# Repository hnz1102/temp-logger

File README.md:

<div align="center">
  <h1><code>Temperature Logger for K-Type Thermocouple</code></h1>
  
</div>

# TempLogger - Temperature Logger for K-Type Thermocouple

This board provides a logging function that gets data on temperature from a K-type thermocouple.

# Feature

**Microcontroller on board** - No need for a PC when you are measuring a temperature.

**Transfer Temperature data via WiFi** - This Logger can transfer temperature data to Linux PC via WiFi network and you can see the dashboard graph in influxDB.

**Battery Powered** - Using LiPo battery. It can run for 48 hours.

# How to use the TempLogger
Put on the thermocouple where you want to measure the temperature.  

Push the START/STOP button, then TempLogger starts to log the temperature. And if you want to send data on temperature, push the SEND button. During the measurement, TempLogger can send the data to a PC. 

A display can show you the current temperature, battery voltage, and WiFi connection status.

If WiFi could not connect to WiFi Access Point, the WiFi mark won't be shown on the display.

You can see the realtime data using Dashboard by [InfluxDB](https://www.influxdata.com/influxdb/).

After the measure, to stop logging, push the START/STOP button again.

To charge a battery, just connect to a USB mini-B port from the bus-powered USB port. During the charge, the CHG LED is RED ON. After the charging is full, the FUL LED is GREEN ON. And the charging will be stopped automatically. But, 

DO NOT CONTINUE THE CHARGE IF THE BATTERY IS FULL FOR A LONG TIME. 

# Case

There are data for 3D printer in `hardware/*.stl`.

# How to build code

Using Ubuntu 22.04.02 LTS

1. Install Rust Compiler
```bash
$ sudo apt -y install git python3 python3-pip gcc build-essential curl pkg-config libudev-dev libtinfo5 clang libclang-dev llvm-dev udev
$ curl --proto '=https' --tlsv1.2 -sSf https://sh.rustup.rs | sh
select No.1
$ source "$HOME/.cargo/env"
```

2. Install toolchain for ESP32-C3
```bash
$ cargo install ldproxy
$ cargo install espup
$ rustup toolchain install nightly --component rust-src
$ rustup target add riscv32imc-unknown-none-elf
$ cargo install cargo-espflash
```

3. Add UDEV rules
```bash
$ sudo sh -c 'echo "SUBSYSTEMS==\"usb\", ATTRS{idVendor}==\"303a\", ATTRS{idProduct}==\"1001\", MODE=\"0666\"" > /etc/udev/rules.d/99-esp32.rules'
$ sudo udevadm control --reload-rules
$ sudo udevadm trigger
```

4. Download Temp-Logger code
```bash
$ git clone https://github.com/hnz1102/temp-logger.git
$ cd temp-logger/src/temp-logger
``` 
5. Setting WiFi SSID, Password, and InfluxDB server IP address.
```bash
src\temp-logger\cfg.toml

[templogger]
wifi_ssid = "<your-AP-ssid>"     # Set your AP ssid.
wifi_psk = "<your-AP-Password>"  # Set password for ssid
http_server = "<PC address>:3000" # Set IP address and port. port should be 3000.
```

6. Connecting the board and Set device and set toolchain.
```bash
Connecting the Temp-Logger by USB to this build code PC. Then, 
$ cargo espflash board-info
select /dev/ttyACM0
Chip type:         esp32c3 (revision v0.4)
Crystal frequency: 40MHz
Flash size:        4MB
Features:          WiFi, BLE
MAC address:       xx:xx:xx:xx:xx:xx

$ rustup component add rust-src --toolchain nightly-2023-06-10-x86_64-unknown-linux-gnu
```

7. Build code and writing flash
```bash
$ cargo espflash flash --release --monitor
App/part. size:    950,864/3,145,728 bytes, 30.23%
[00:00:00] [========================================]      12/12      0x0                                                                       
[00:00:00] [========================================]       1/1       0x8000                                                                    
[00:00:11] [========================================]     535/535     0x10000                                                                   [2023-08-03T13:05:12Z INFO ] Flashing has completed!

And automaticaly boot!
```

# How to Install the influxDB and Agent

1. Download [influxDB](https://docs.influxdata.com/influxdb/v2.7/install/?t=Linux) and Install.
```bash
$ wget https://dl.influxdata.com/influxdb/releases/influxdb2-2.7.0-amd64.deb
$ sudo dpkg -i influxdb2-2.7.0-amd64.deb
$ sudo service influxdb start
```

2. Configure the influxDB

```
Connect to the 'http://<influxDB installed PC Address>:8086'
```

Click `GET STARTED` and set `Username`, `Password`, `Initial Organization Name`, and `Initial Bucket Name`
|Term|Value|
|---|---|
|Username|Set login username as influxDB administrator web console|
|Password|Set login password as influxDB administrator web console|
|Initial Organization Name| Organization Name ex. ORG|
|Initail Bucket Name| LOGGER |

After set them, click `CONTINUE`.

3. Copy the operator API token.

You can see the operator API token on the browser. YOU WON'T BE ABLE TO SEE IT AGAIN!

After copy the token, click `CONFIGURE LATER`.

4. Import the Dashboard Template.

Click the `Dashboard` icon, and select `Import Dashboard` from the `CREATE DASHBOARD` menu.

Drop the `src/server/temp-logger_dashboard.json` file to `Drop a file here`, then click `IMPORT JSON AS DASHBOARD`.

You can see the `Temp-Logger Dashboard` pannel on the Dashboards page.

Click this panel, and You can see the Temp-Logger Dashboard.

If you want to customize the dashboard design, click configure mark. You can change the graph design.

5. Install the Agent.

Temp-Logger can't directly send data to influxDB API since ESP32-C3 has not TLS software stack. This agent program is responsible for changing HTTP communication from Temp-Logger to HTTPS communication and passing data to the InfluxDB API. This agent is purpose only for a local network because it has no security.

Before install you have to change parameters in main.js.

src/server/main.js
```javascript
const token = "<influxDB API Access Token>"
const url = 'http://<influxDB installed IP address>:8086'
let org = `<YOUR ORGANIZATION NAME: it has to be same the Initial Organization Name>`
let bucket = `LOGGER`
```

Install the agent program.

```bash
$ cd src/server/
$ ./install.sh
```
If it is `Active: active`` as shown below, it has started normally.
```
● influxdb-agent.service - InfluxDB Agent
     Loaded: loaded (/lib/systemd/system/influxdb-agent.service; enabled; vendor preset: enabled)
     Active: active (running) since Sat 2023-08-05 02:24:18 UTC; 15ms ago
```

6. Start Temp-Logger Logging and Send Data.

Push the START/STOP button, and push SEND button. Logging data will be sent to the influxDB. You can see the data on the dashboard.

# Add Battery Monitor

A small modification was made to monitor the battery voltage.

I already fixed new PCB gerber data.

## LICENSE
This source code is licensed under MIT. Other Hardware Schematic documents are licensed under CC-BY-SA V4.0.

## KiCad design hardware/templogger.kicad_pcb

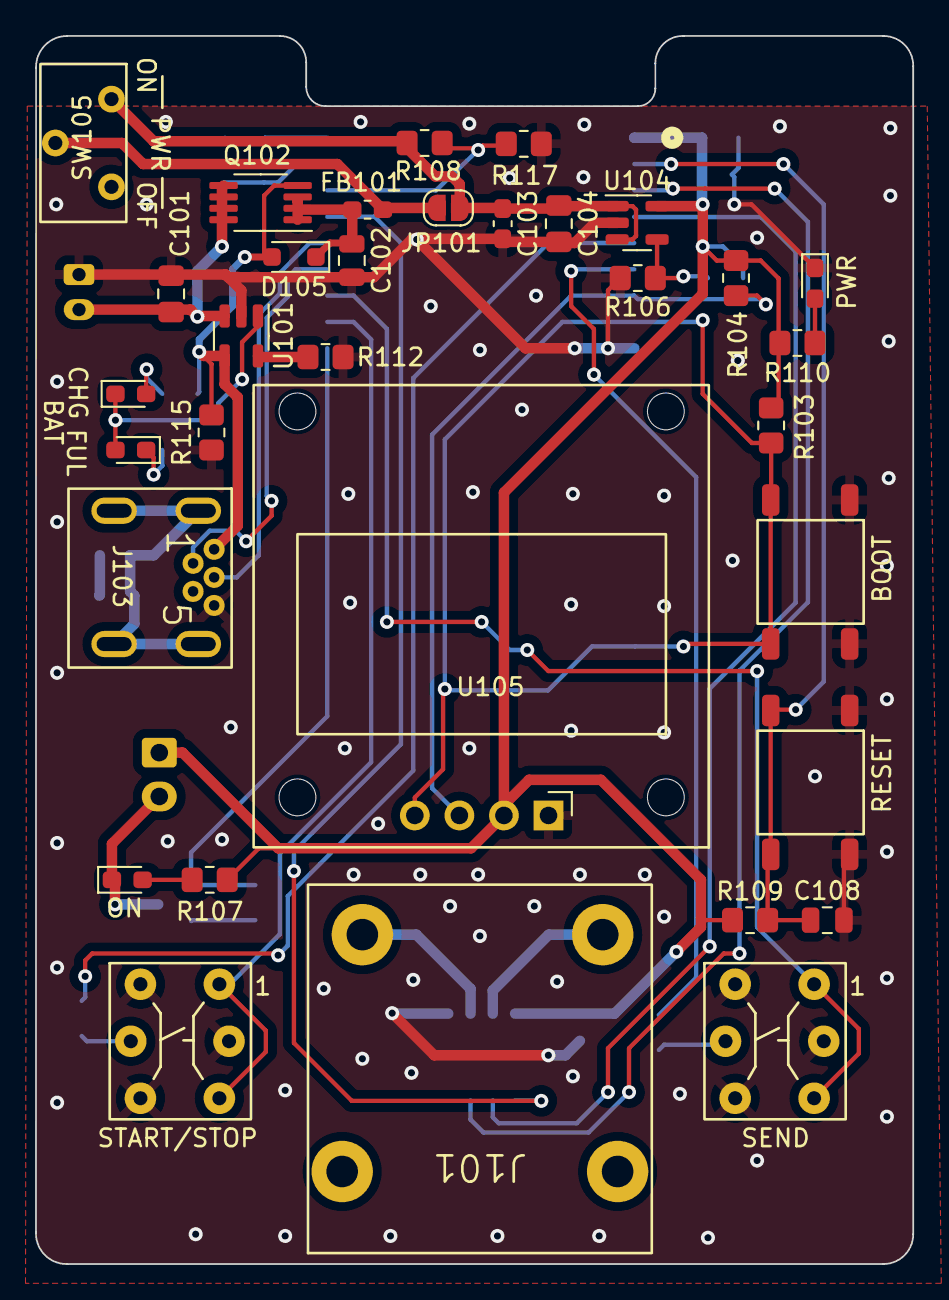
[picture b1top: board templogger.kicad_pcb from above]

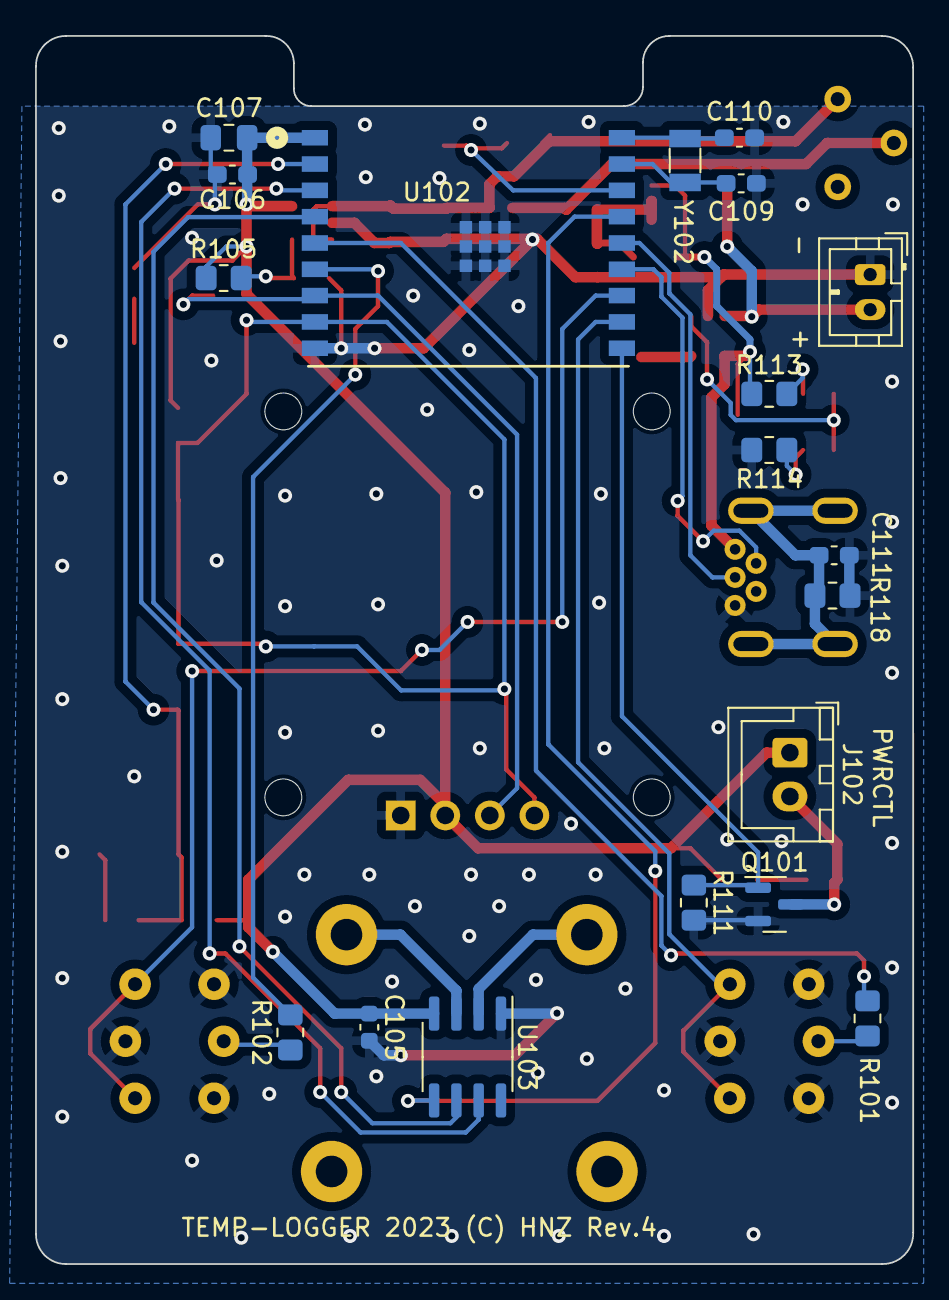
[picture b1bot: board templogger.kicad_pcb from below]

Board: 2 copper layers, 50.0 x 70.0 mm, 52 parts (19 on the bottom side), 36 nets.

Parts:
C101: 4.7uF; C_0805_2012Metric_Pad1.18x1.45mm_HandSolder
C102, C108: 1uF; C_0805_2012Metric
C103, C106, C111: 0.1uF; C_0603_1608Metric_Pad1.08x0.95mm_HandSolder
C104, C107: 10uF; C_0805_2012Metric_Pad1.18x1.45mm_HandSolder
C105: 0.1uF; C_0603_1608Metric
C109, C110: 16pF; C_0603_1608Metric_Pad1.08x0.95mm_HandSolder
D101, D102, D103: LED RED SML-E12V8WT86; LED_0603_1608Metric_Pad1.05x0.95mm_HandSolder
D104: LED GREEN SML-E12P8WT86; LED_0603_1608Metric_Pad1.05x0.95mm_HandSolder
D105: NSR0340HT1G; D_SOD-323_HandSoldering
FB101: BK2125HS601-T; L_0603_1608Metric_Pad1.05x0.95mm_HandSolder
J101: Conn_K_TERM_XH_2P; PCC-SMP_D
J102: Conn_01x02; JST_XH_B2B-XH-A_1x02_P2.50mm_Vertical
J103: USB_B_Mini; usb mini B connector c2235 dim 2
J104: LiPo BATTERY Socket; JST_PH_B2B-PH-K_1x02_P2.00mm_Vertical
JP101: SolderJumper_2_Open; SolderJumper-2_P1.3mm_Open_RoundedPad1.0x1.5mm
Q101: 2N7002K; SOT-23
Q102: IRF7606TRPBF; MSOP-8_3x3mm_P0.65mm
R101, R102, R107, R110, R113, R114: 330; R_0805_2012Metric_Pad1.20x1.40mm_HandSolder
R103, R104, R109, R111, R118: 10K; R_0805_2012Metric_Pad1.20x1.40mm_HandSolder
R105, R108, R117: 20K 1%; R_0805_2012Metric_Pad1.20x1.40mm_HandSolder
R106: 12K 1%; R_0805_2012Metric_Pad1.20x1.40mm_HandSolder
R112: 2K; R_0805_2012Metric_Pad1.20x1.40mm_HandSolder
R115: 100K; R_0805_2012Metric_Pad1.20x1.40mm_HandSolder
SW101, SW102: SW_Push_LED; LS601-CU_CAP
SW103: BOOT TS-06104; TS-06104
SW104: RESET TS-06104; TS-06104
SW105: SLIDE_SW IS-1245T-G; SLIDE_SW_IS1235-G
U101: MCP73831-2-OT; SOT-23-5
U102: ESP32-C3-WROOM-02-N4; IC18_ESP32-C3-WROOM-02-N4_EXP
U103: MAX31855KASA; SOIC-8_3.9x4.9mm_P1.27mm
U104: SPX3819M5-L; SOT-23-5
U105: SSD1306_DISPLAY; OLED I2C DISPLAY
Y102: 32.7680KHz; Crystal_SMD_3215-2Pin_3.2x1.5mm

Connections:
+3.3V: C105.1, C106.1, C107.1, J102.1, R103.1, R104.1, R105.1, R107.1, R109.1, R110.1, U102.1 (3V3), U103.4 (V_CC), U104.5 (OUT), U105.2 (VCC)
/GPIO0: C110.1, U102.18 (IO0), Y102.2
/GPIO1: C109.1, U102.17 (IO1), Y102.1
/GPIO2: R108.2, R117.1, U102.16 (IO2)
/GPIO3: U102.15 (IO3), U103.5 (SCK)
/GPIO4/TMS: U102.3 (IO4), U103.7 (SO)
/GPIO5/TDI: U102.4 (IO5), U103.6 (~CS)
/GPIO6/TCK: R101.2, U102.5 (IO6)
/GPIO7/TDO: R102.2, U102.6 (IO7)
/GPIO8: R104.2, U102.7 (IO8), U105.3 (SCL)
/GPIO9: R103.2, SW103.A, SW103.B, U102.8 (IO9), U105.4 (SDA)
/GPIO10: Q101.1 (G), R111.1, U102.10 (IO10)
/RXD/GPIO20: SW101.1, SW101.2, U102.11 (RXD)
/TXD/GPIO21: SW102.1, SW102.2, U102.12 (TXD)
/USBVDD: D105.2 (A), J103.1 (VBUS), Q102.4 (G), R113.1, R115.1, U101.4 (V_{DD})
/VBAT: C101.1, J104.2, Q102.5 (D), Q102.6 (D), Q102.7 (D), Q102.8 (D), U101.3 (V_{BAT})
/VIN: C103.1, C104.1, JP101.2 (B), R108.1, SW105.1 (A), U104.1 (IN), U104.3 (EN)
/VOUT: C102.1, D105.1 (K), FB101.1, Q102.1 (S), Q102.2 (S), Q102.3 (S)
/~RESET: C108.1, R109.2, SW104.A, SW104.B, U102.2 (EN)
GND: C101.2, C102.2, C103.2, C104.2, C105.2, C106.2, C107.2, C108.2, C109.2, C110.2, C111.2, D103.1 (K), J103.5 (GND), J104.1, Q101.2 (S), R106.2, R111.2, R112.2, R114.2, R115.2, R117.2, R118.2, SW101.3, SW101.4, SW101.6 (K), SW102.3, SW102.4, SW102.6 (K), SW103.C, SW103.D, SW104.C, SW104.D, U101.2 (V_{SS}), U102.9 (GND), U102.19 (GND), U102.20 (GND), U102.21 (GND), U102.22 (GND), U102.23 (GND), U102.24 (GND), U102.25 (GND), U102.26 (GND), U102.27 (GND), U103.1 (GND), U104.2 (GND), U105.1 (GND)
unnamed: D101.2 (A), R107.2
unnamed: D101.1 (K), J102.2, Q101.3 (D)
unnamed: D102.2 (A), R113.2
unnamed: D102.1 (K), D104.2 (A), U101.1 (STAT)
unnamed: D103.2 (A), R110.2
unnamed: D104.1 (K), R114.1
unnamed: J103.3 (D+), U102.14 (IO19)
unnamed: J103.2 (D-), U102.13 (IO18)
unnamed: C111.1, J103.6 (Shield), R118.1
unnamed: FB101.2, JP101.1 (A), SW105.2 (B)
unnamed: R101.1, SW101.5 (A)
unnamed: R102.1, SW102.5 (A)
unnamed: R112.1, U101.5 (PROG)
unnamed: J101.+, U103.3 (T+)
unnamed: J101.-, U103.2 (T-)
unnamed: R105.2, R106.1, U104.4 (ADJ)

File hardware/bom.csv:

Reference,Value,Footprint,akizuki,digikey,storeURL,Qty
C101,4.7uF,Capacitor_SMD:C_0805_2012Metric_Pad1.18x1.45mm_HandSolder,,311-1455-1-ND,https://www.digikey.com/en/products/detail/yageo/CC0603KRX5R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,1
"C102, C108",1uF,Capacitor_SMD:C_0805_2012Metric,,13-CC0603KPX7R7BB105CT-ND,https://www.digikey.com/en/products/detail/yageo/CC0603KPX7R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,2
"C103, C106, C111",0.1uF,Capacitor_SMD:C_0603_1608Metric_Pad1.08x0.95mm_HandSolder,,311-1824-1-ND,https://www.digikey.com/en/products/detail/yageo/CC0603MRX7R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,3
"C104, C107",10uF,Capacitor_SMD:C_0805_2012Metric_Pad1.18x1.45mm_HandSolder,,311-3494-1-ND,https://www.digikey.com/en/products/detail/yageo/CC0603MRX5R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,2
C105,0.1uF,Capacitor_SMD:C_0603_1608Metric,,311-1824-1-ND,https://www.digikey.com/en/products/detail/yageo/CC0603MRX7R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,1
"C109, C110",16pF,Capacitor_SMD:C_0603_1608Metric_Pad1.08x0.95mm_HandSolder,,311-1751-1-ND ,https://www.digikey.com/en/products/detail/yageo/CC0603JRNPO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,2
D101-D103,LED RED SML-E12V8WT86,tbctl:LED_0603_1608Metric_Pad1.05x0.95mm_HandSolder,,511-1587-1-ND,https://www.digikey.com/en/products/detail/rohm-semiconducto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,3
D104,LED GREEN SML-E12P8WT86,tbctl:LED_0603_1608Metric_Pad1.05x0.95mm_HandSolder,,511-1585-1-ND,https://www.digikey.com/en/products/detail/rohm-semiconducto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,1
D105,NSR0340HT1G,Diode_SMD:D_SOD-323_HandSoldering,,NSR0340HT1GOSCT-ND,https://www.digikey.com/en/products/detail/onsemi/NSR0340HT1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,1
FB101,BK2125HS601-T,tbctl:L_0603_1608Metric_Pad1.05x0.95mm_HandSolder,,240-2399-1-ND,https://www.digikey.com/en/products/detail/laird-signal-inte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,1
J101,Conn_K_TERM_XH_2P,tbctl:PCC-SMP_D,P-14972,1568-1306-ND,https://www.digikey.com/en/products/detail/sparkfun-electron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,1
J102,Conn_01x02,Connector_JST:JST_XH_B2B-XH-A_1x02_P2.50mm_Vertical,C-12247,455-2247-ND,https://www.digikey.com/en/products/detail/jst-sales-america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,1
J103,USB_B_Mini,tbctl:usb mini B connector c2235 dim 2,C-02235,,https://akizukidenshi.com/catalog/g/gC-02235/,1
J104,LiPo BATTERY Socket,Connector_JST:JST_PH_B2B-PH-K_1x02_P2.00mm_Vertical,C-12802,455-1704-ND,https://www.digikey.com/en/products/detail/jst-sales-america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,1
JP101,SolderJumper_2_Open,Jumper:SolderJumper-2_P1.3mm_Open_RoundedPad1.0x1.5mm,,,,1
Q101,2N7002K,Package_TO_SOT_SMD:SOT-23,,2N7002K-7DICT-ND,https://www.digikey.com/en/products/detail/diodes-incorporat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,1
Q102,IRF7606TRPBF,Package_SO:MSOP-8_3x3mm_P0.65mm,,IRF7606TRPBFCT-ND,https://www.digikey.com/en/products/detail/infineon-technolo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,1
"R101, R102, R107, R110, R113, R114",330,tbctl:R_0805_2012Metric_Pad1.20x1.40mm_HandSolder,,311-330GRCT-ND,https://www.digikey.com/en/products/detail/yageo/RC0603JR-07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,6
"R103, R104, R109, R111, R118",10K,tbctl:R_0805_2012Metric_Pad1.20x1.40mm_HandSolder,,13-RC0603JR-1010KLCT-ND,https://www.digikey.com/en/products/detail/yageo/RC0603JR-10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,5
"R105, R108, R117",20K 1%,tbctl:R_0805_2012Metric_Pad1.20x1.40mm_HandSolder,,13-RC0603FR-1320KLCT-ND,https://www.digikey.com/en/products/detail/yageo/RC0603FR-13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,3
R106,12K 1%,tbctl:R_0805_2012Metric_Pad1.20x1.40mm_HandSolder,,311-12.0KHRCT-ND,https://www.digikey.com/en/products/detail/yageo/RC0603FR-07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,1
R112,2K,tbctl:R_0805_2012Metric_Pad1.20x1.40mm_HandSolder,,311-2.0KGRCT-ND,https://www.digikey.com/en/products/detail/yageo/RC0603JR-07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,1
R115,100K,tbctl:R_0805_2012Metric_Pad1.20x1.40mm_HandSolder,,311-100KGRCT-ND,https://www.digikey.com/en/products/detail/yageo/RC0603JR-07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,1
SW101,SW_Push_LED,tbctl:LS601-CU_CAP,,,https://akizukidenshi.com/catalog/g/gP-13871/,1
SW102,SW_Push_LED,tbctl:LS601-CU_CAP,,,https://akizukidenshi.com/catalog/g/gP-13870/,1
SW103,BOOT TS-06104,tbctl:TS-06104,P-15969,,https://akizukidenshi.com/catalog/g/gP-15969/,1
SW104,RESET TS-06104,tbctl:TS-06104,P-15969,,https://akizukidenshi.com/catalog/g/gP-15969/,1
SW105,SLIDE_SW IS-1245T-G,tbctl:SLIDE_SW_IS1235-G,P-15368,,https://akizukidenshi.com/catalog/g/gP-15368/,1
U101,MCP73831-2-OT,Package_TO_SOT_SMD:SOT-23-5,I-13288,MCP73831T-2ACI/OTCT-ND,https://www.digikey.com/en/products/detail/microchip-technol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,1
U102,ESP32-C3-WROOM-02-N4,tbctl:IC18_ESP32-C3-WROOM-02-N4_EXP,M-17493,1965-ESP32-C3-WROOM-02-N4CT-ND,https://www.digikey.com/en/products/detail/espressif-systems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,1
U103,MAX31855KASA,Package_SO:SOIC-8_3.9x4.9mm_P1.27mm,I-14486,MAX31855KASA+TCT-ND,https://www.digikey.com/en/products/detail/analog-devices-in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,1
U104,SPX3819M5-L,Package_TO_SOT_SMD:SOT-23-5,,1016-1871-1-ND,https://www.digikey.com/en/products/detail/maxlinear-inc/SPX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,1
U105,SSD1306_DISPLAY,tbctl:OLED I2C DISPLAY,,,https://www.amazon.co.jp/gp/product/B08CTZVVLS/,1
Y102,32.7680KHz,Crystal:Crystal_SMD_3215-2Pin_3.2x1.5mm,,2151-RT3215-32.768-12.5-TRCT-ND,https://www.digikey.com/en/products/detail/raltron-electroni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,1

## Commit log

2023-08-03 Add how to build code
2023-08-04 Add dashboard template
2023-08-05 Add install script for agent
2023-08-06 Add gerber file and update BOM list
2023-08-06 remove UTF characters
2023-08-08 clean up code
2023-08-12 Change new font
2023-08-12 Change photos
2023-08-12 Fixed to read max31855 when it's minus temperature
2023-08-24 Fixed battery socket
2023-08-24 Add usb power icon
2023-08-24 update photo
2023-08-28 Add case data for 3d printer
2023-08-28 Update bom list
2023-09-03 Fixed a pcb edge line.
2023-09-04 Update case design
2023-09-04 Fixed typo
